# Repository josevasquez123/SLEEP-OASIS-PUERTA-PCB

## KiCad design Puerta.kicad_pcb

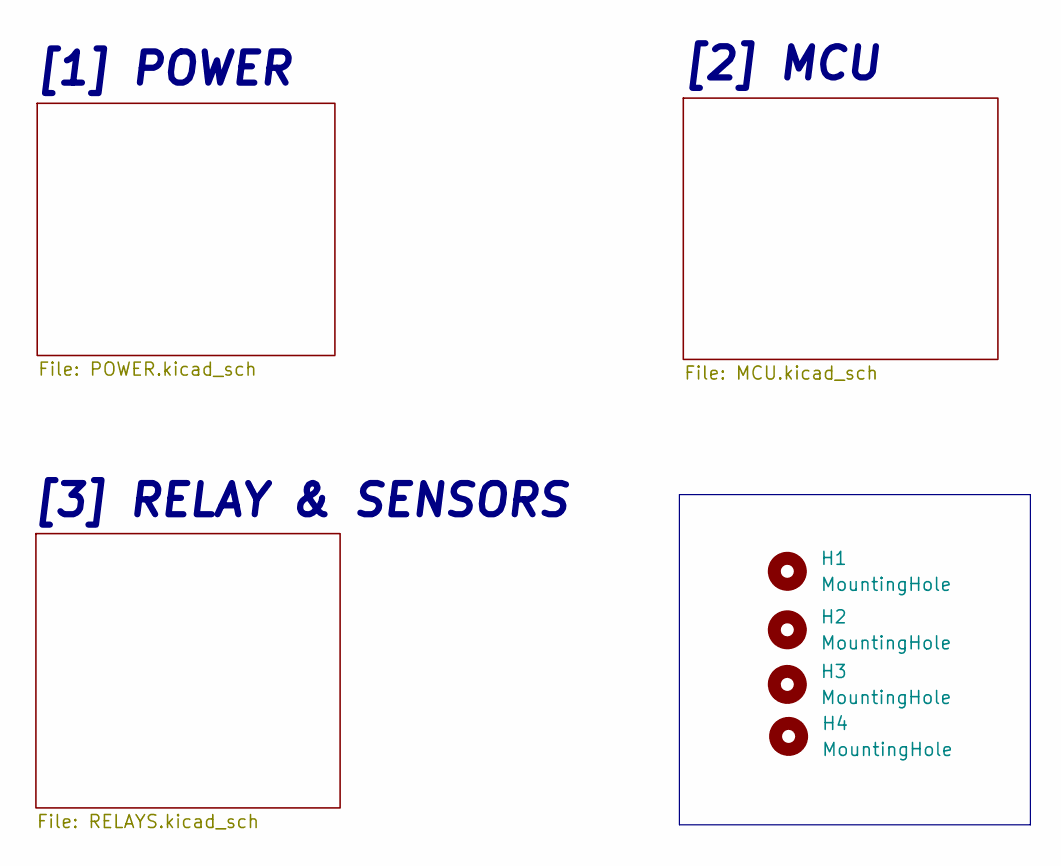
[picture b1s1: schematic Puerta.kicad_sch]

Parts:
H1, H2, H3, H4: MountingHole; MountingHole_3.2mm_M3

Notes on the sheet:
[1] POWER
[3] RELAY & SENSORS
[2] MCU

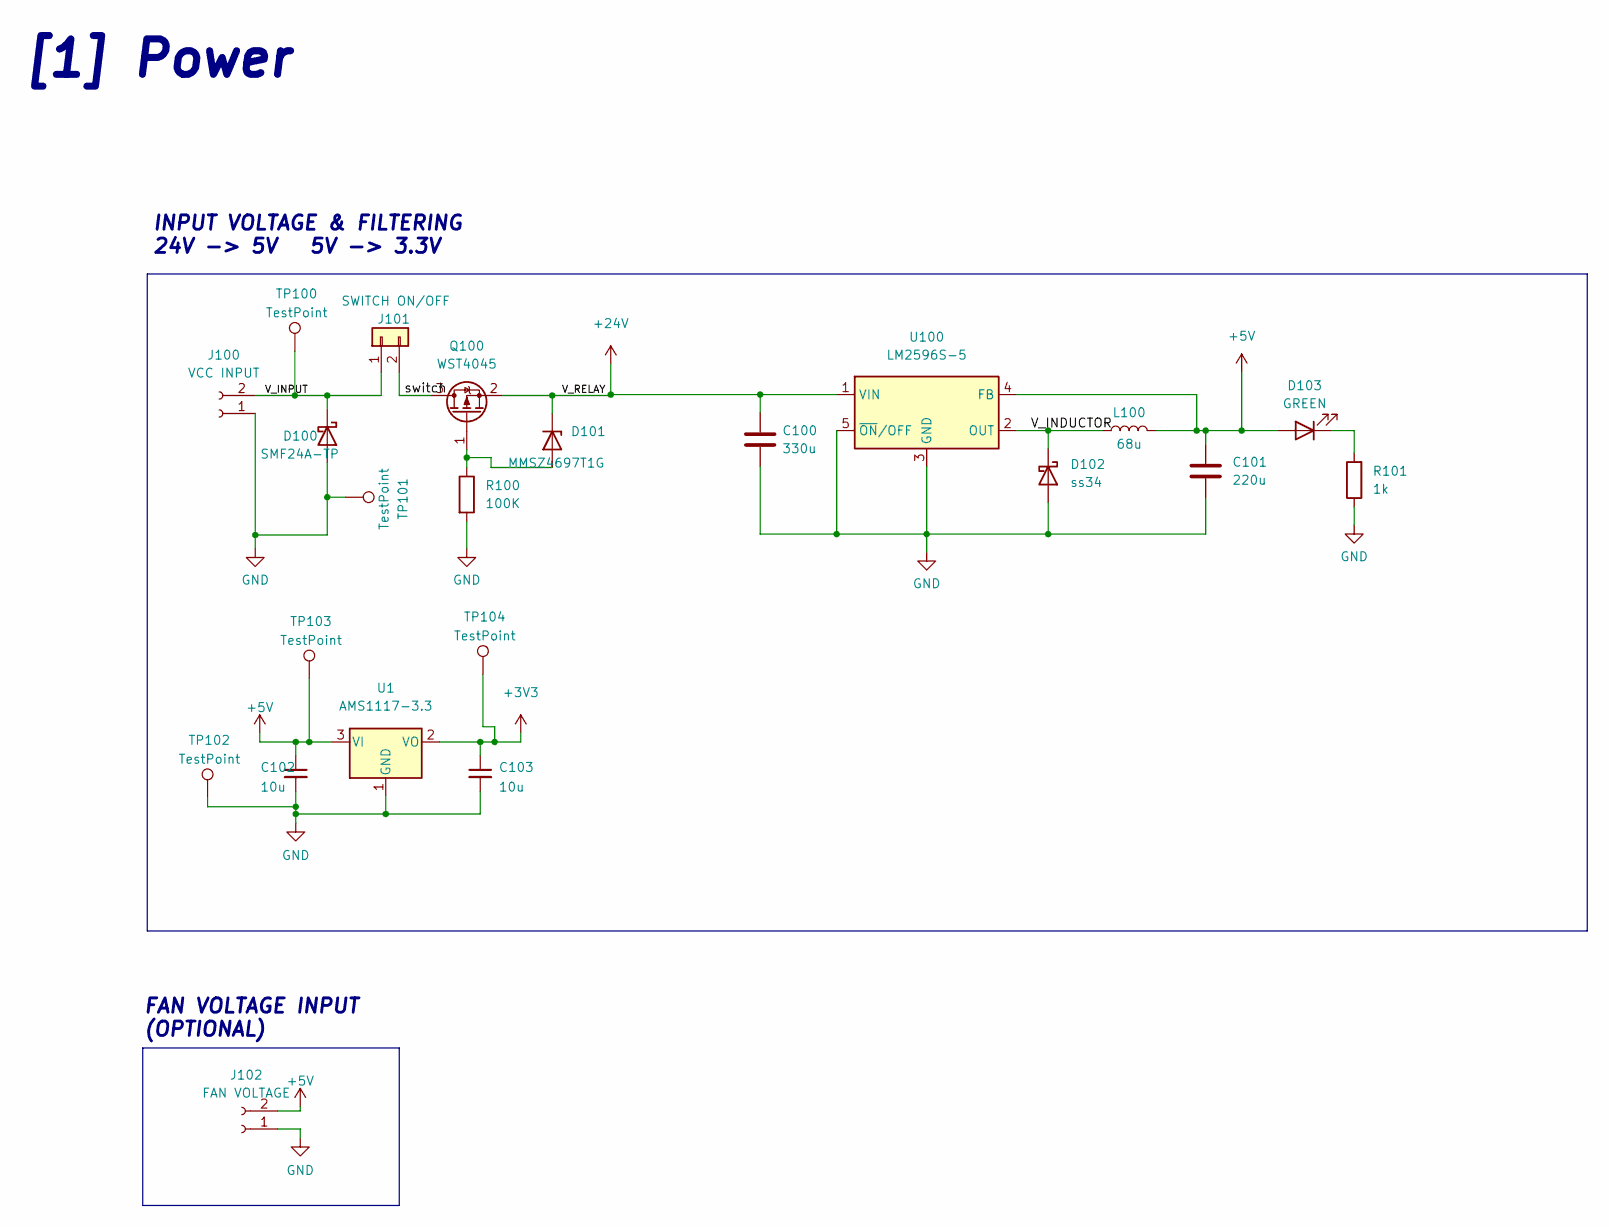
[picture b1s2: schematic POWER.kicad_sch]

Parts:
C100: 330u; C_Elec_10x10.2; LCSC C239324
C101: 220u; CP_Elec_10x10.5; LCSC C2886113
C102, C103: 10u; C_0805_2012Metric; LCSC C15850
D100: SMF24A-TP; SOD_123FL; LCSC C545276
D101: MMSZ4697T1G; D_SOD-123; LCSC C48870
D102: ss34; D_SMA; LCSC C8678
D103: GREEN; LED_0603_1608Metric; LCSC C72043
J100: VCC INPUT; PhoenixContact_MSTBA_2,5_2-G-5,08_1x02_P5.08mm_Horizontal
J101: SWITCH ON/OFF; JST_B2B-XH-A_LF__SN_
J102: FAN VOLTAGE; PinHeader_1x02_P2.54mm_Vertical
L100: 68u; L_12.3x12.3; LCSC C2929504
Q100: WST4045; SOT-23; LCSC C719073
R100: 100K; R_1206_3216Metric; LCSC C17900
R101: 1k; R_0603_1608Metric; LCSC C21190
TP100, TP101, TP102, TP103, TP104: TestPoint; TestPoint_Pad_D2.0mm
U1: AMS1117-3.3; SOT-223-3_TabPin2; LCSC C6186
U100: LM2596S-5; TO-263-5_TabPin3

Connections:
+5V: C101.1, C102.1, D103.2 (A), J102.2, L100.2, TP103.1, U1.3 (VI), U100.4 (FB); also elsewhere on the board
+24V: C100.1, D101.1 (K), Q100.2 (S), U100.1 (VIN); also elsewhere on the board
/POWER/V_INDUCTOR: D102.1 (K), L100.1, U100.2 (OUT)
/POWER/V_INPUT: D100.1 (K), J100.2, J101.1, TP100.1
/POWER/switch: J101.2, Q100.3 (D)
GND: C100.2, C101.2, C102.2, C103.2, D100.2 (A), D102.2 (A), J100.1, J102.1, R100.2, R101.1, TP101.1, TP102.1, U1.1 (GND), U100.3 (GND), U100.5 (~ON/OFF); also elsewhere on the board
unnamed: D101.2 (A), Q100.1 (G), R100.1
unnamed: D103.1 (K), R101.2

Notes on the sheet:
INPUT VOLTAGE & FILTERING 24V -> 5V 5V -> 3.3V
FAN VOLTAGE INPUT (OPTIONAL)
[1] Power

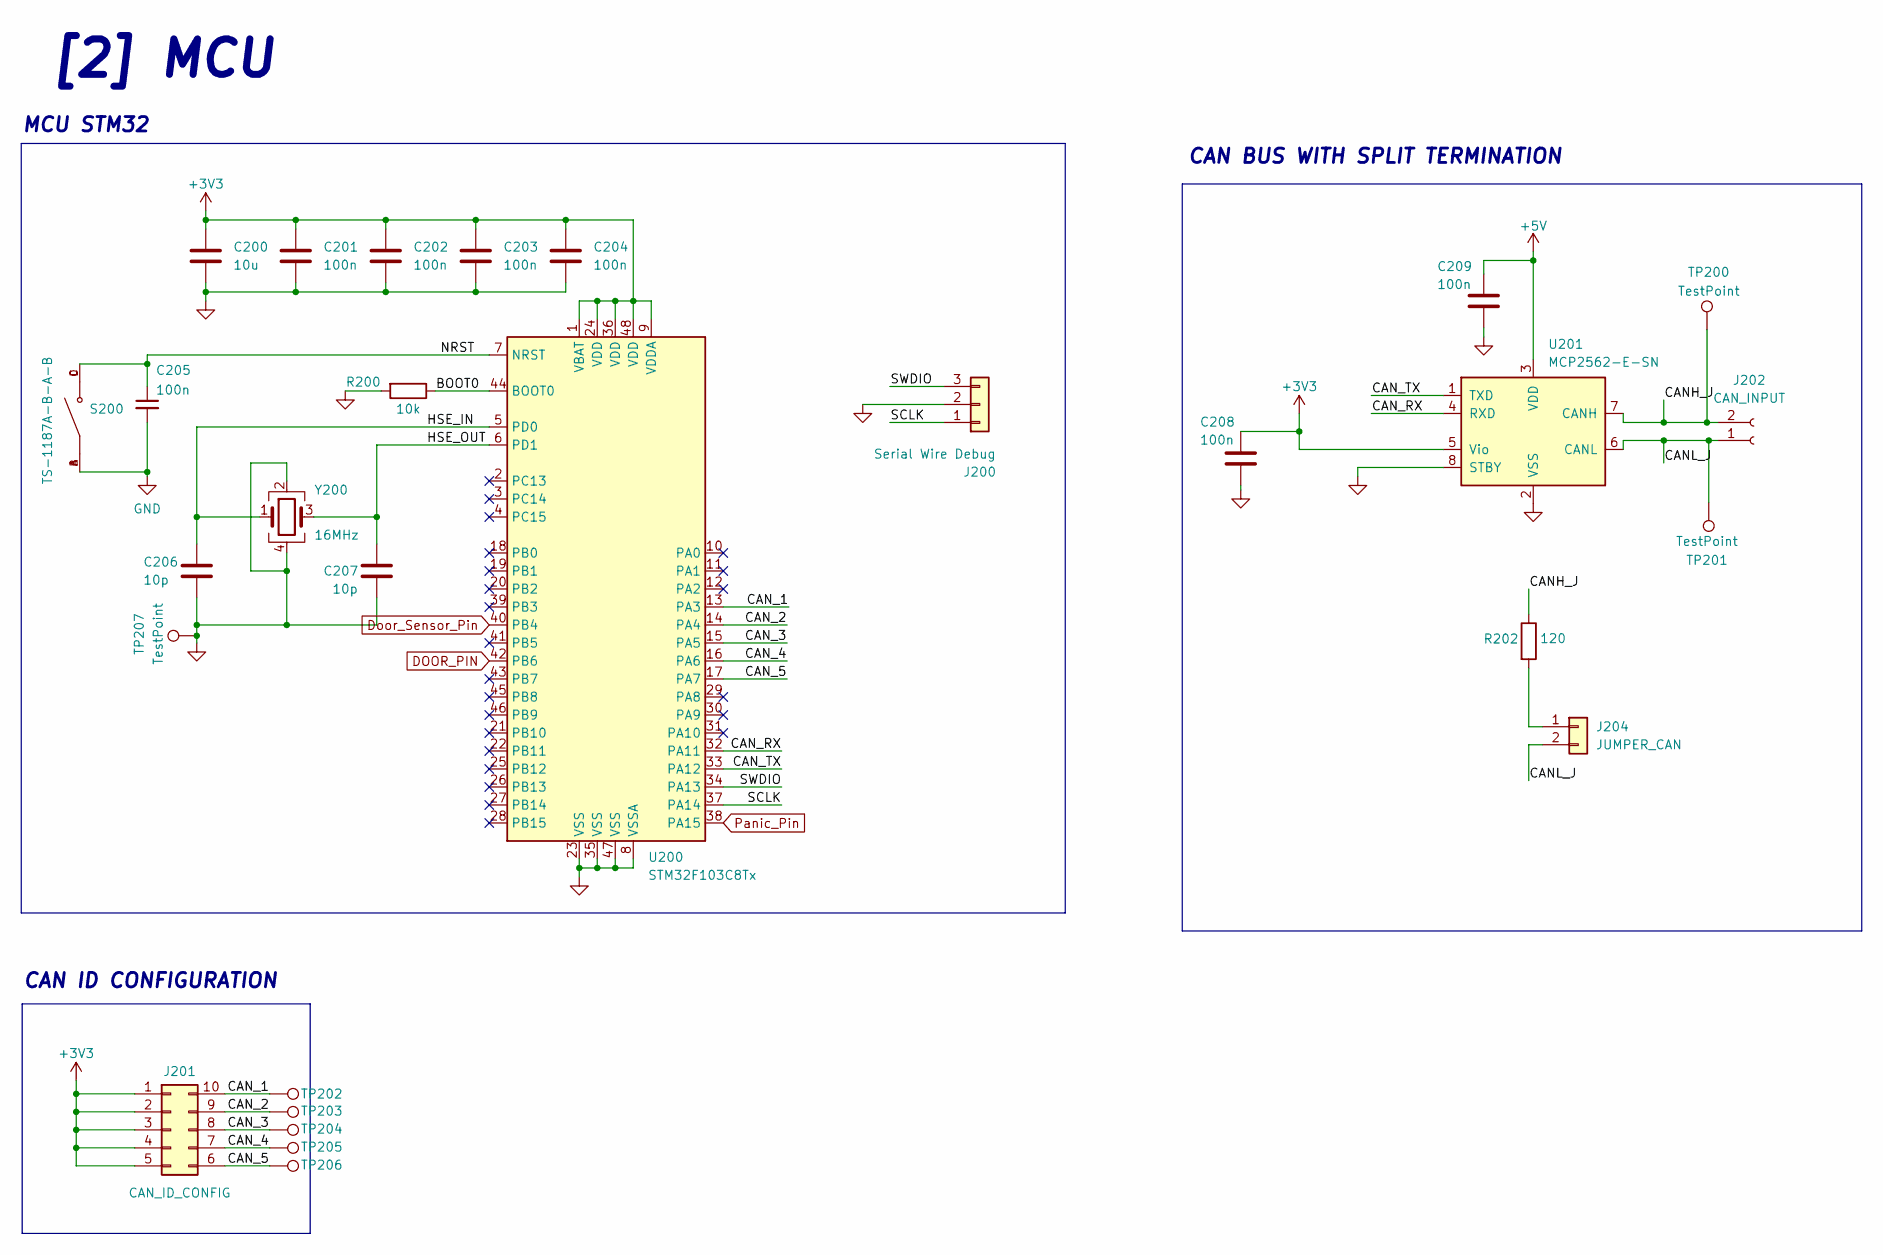
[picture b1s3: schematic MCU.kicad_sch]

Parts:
C200: 10u; C_0603_1608Metric; LCSC C19702
C201, C202, C203, C204, C205, C208, C209: 100n; C_0402_1005Metric; LCSC C1525
C206, C207: 10p; C_0402_1005Metric; LCSC C32949
J200: Serial Wire Debug; PinSocket_1x03_P2.54mm_Vertical
J201: CAN_ID_CONFIG; SW_DIP_SPSTx05_Slide_9.78x14.88mm_W7.62mm_P2.54mm
J202: CAN_INPUT; PhoenixContact_MSTBA_2,5_2-G-5,08_1x02_P5.08mm_Horizontal
J204: JUMPER_CAN; PinHeader_1x02_P2.54mm_Vertical
R200: 10k; R_0402_1005Metric; LCSC C25744
R202: 120; R_0805_2012Metric; LCSC C17437
S200: TS-1187A-B-A-B; SWITCH_SMD; LCSC C318884
TP200, TP201, TP202, TP203, TP204, TP205, TP206, TP207: TestPoint; TestPoint_Pad_D2.0mm
U200: STM32F103C8Tx; LQFP-48_7x7mm_P0.5mm
U201: MCP2562-E-SN; SOIC-8_3.9x4.9mm_P1.27mm; LCSC C191417
Y200: 16MHz; Crystal_SMD_3225-4Pin_3.2x2.5mm; LCSC C13738

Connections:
+5V: C209.1, U201.3 (VDD); also elsewhere on the board
/MCU/BOOT0: R200.1, U200.44 (BOOT0)
/MCU/CANH_J: J202.2, R202.1, TP200.1, U201.7 (CANH)
/MCU/CANL_J: J202.1, J204.2, TP201.1, U201.6 (CANL)
/MCU/CAN_1: J201.10, TP202.1, U200.13 (PA3)
/MCU/CAN_2: J201.9, TP203.1, U200.14 (PA4)
/MCU/CAN_3: J201.8, TP204.1, U200.15 (PA5)
/MCU/CAN_4: J201.7, TP205.1, U200.16 (PA6)
/MCU/CAN_5: J201.6, TP206.1, U200.17 (PA7)
/MCU/CAN_RX: U200.32 (PA11), U201.4 (RXD)
/MCU/CAN_TX: U200.33 (PA12), U201.1 (TXD)
/MCU/HSE_IN: C206.1, U200.5 (PD0), Y200.1
/MCU/HSE_OUT: C207.1, U200.6 (PD1), Y200.3
/MCU/NRST: C205.1, S200.C, S200.D, U200.7 (NRST)
/MCU/SCLK: J200.1, U200.37 (PA14)
/MCU/SWDIO: J200.3, U200.34 (PA13)
DOOR_PIN: U200.42 (PB6); also elsewhere on the board
Door_Sensor_Pin: U200.40 (PB4); also elsewhere on the board
GND: C200.2, C201.2, C202.2, C203.2, C204.2, C205.2, C206.2, C207.2, C208.2, C209.2, J200.2, R200.2, S200.A, S200.B, TP207.1, U200.8 (VSSA), U200.23 (VSS), U200.35 (VSS), U200.47 (VSS), U201.2 (VSS), U201.8 (STBY), Y200.2, Y200.4; also elsewhere on the board
unnamed: J204.1, R202.2
Panic_Pin: U200.38 (PA15); also elsewhere on the board

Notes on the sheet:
[2] MCU
MCU STM32
CAN ID CONFIGURATION
CAN BUS WITH SPLIT TERMINATION

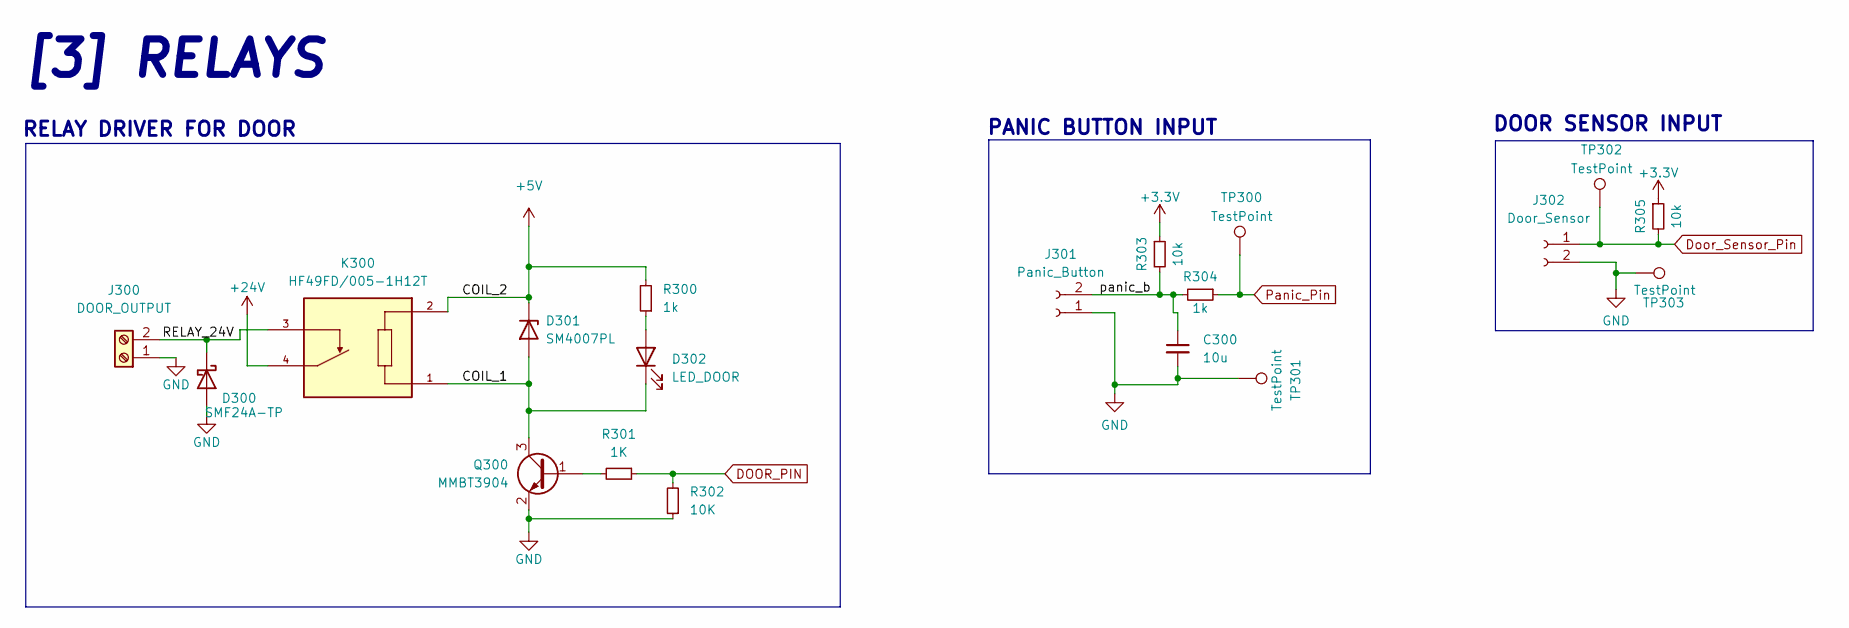
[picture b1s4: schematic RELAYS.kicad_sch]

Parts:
C300: 10u; C_0603_1608Metric; LCSC C19702
D300: SMF24A-TP; SOD_123FL; LCSC C545276
D301: SM4007PL; SOD_123FL; LCSC C64898
D302: LED_DOOR; LED_0603_1608Metric; LCSC C72038
J300: DOOR_OUTPUT; PhoenixContact_MSTBA_2,5_2-G-5,08_1x02_P5.08mm_Horizontal
J301: Panic_Button; PhoenixContact_MSTBA_2,5_2-G-5,08_1x02_P5.08mm_Horizontal
J302: Door_Sensor; PhoenixContact_MSTBA_2,5_2-G-5,08_1x02_P5.08mm_Horizontal
K300: HF49FD/005-1H12T; HF49FD0051H11F; PARTREV 1.13
Q300: MMBT3904; SOT-23; LCSC C20526
R300, R304: 1k; R_0603_1608Metric; LCSC C21190
R301: 1K; R_0603_1608Metric; LCSC C21190
R302: 10K; R_0603_1608Metric; LCSC C25804
R303, R305: 10k; R_0603_1608Metric; LCSC C25804
TP300, TP301, TP302, TP303: TestPoint; TestPoint_Pad_D2.0mm

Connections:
+5V: D301.1 (K), K300.2, R300.2; also elsewhere on the board
+24V: K300.4; also elsewhere on the board
/RELAYS&INPUTS/COIL_1: D301.2 (A), D302.1 (K), K300.1, Q300.3 (C)
/RELAYS&INPUTS/RELAY_24V: D300.1 (K), J300.2, K300.3
/RELAYS&INPUTS/panic_b: C300.1, J301.2, R303.2, R304.2
DOOR_PIN: R301.1, R302.2; also elsewhere on the board
Door_Sensor_Pin: J302.1, R305.2, TP302.1; also elsewhere on the board
GND: C300.2, D300.2 (A), J300.1, J301.1, J302.2, Q300.2 (E), R302.1, TP301.1, TP303.1; also elsewhere on the board
unnamed: D302.2 (A), R300.1
unnamed: Q300.1 (B), R301.2
Panic_Pin: R304.1, TP300.1; also elsewhere on the board

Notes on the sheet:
DOOR SENSOR INPUT
PANIC BUTTON INPUT
[3] RELAYS
RELAY DRIVER FOR DOOR

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
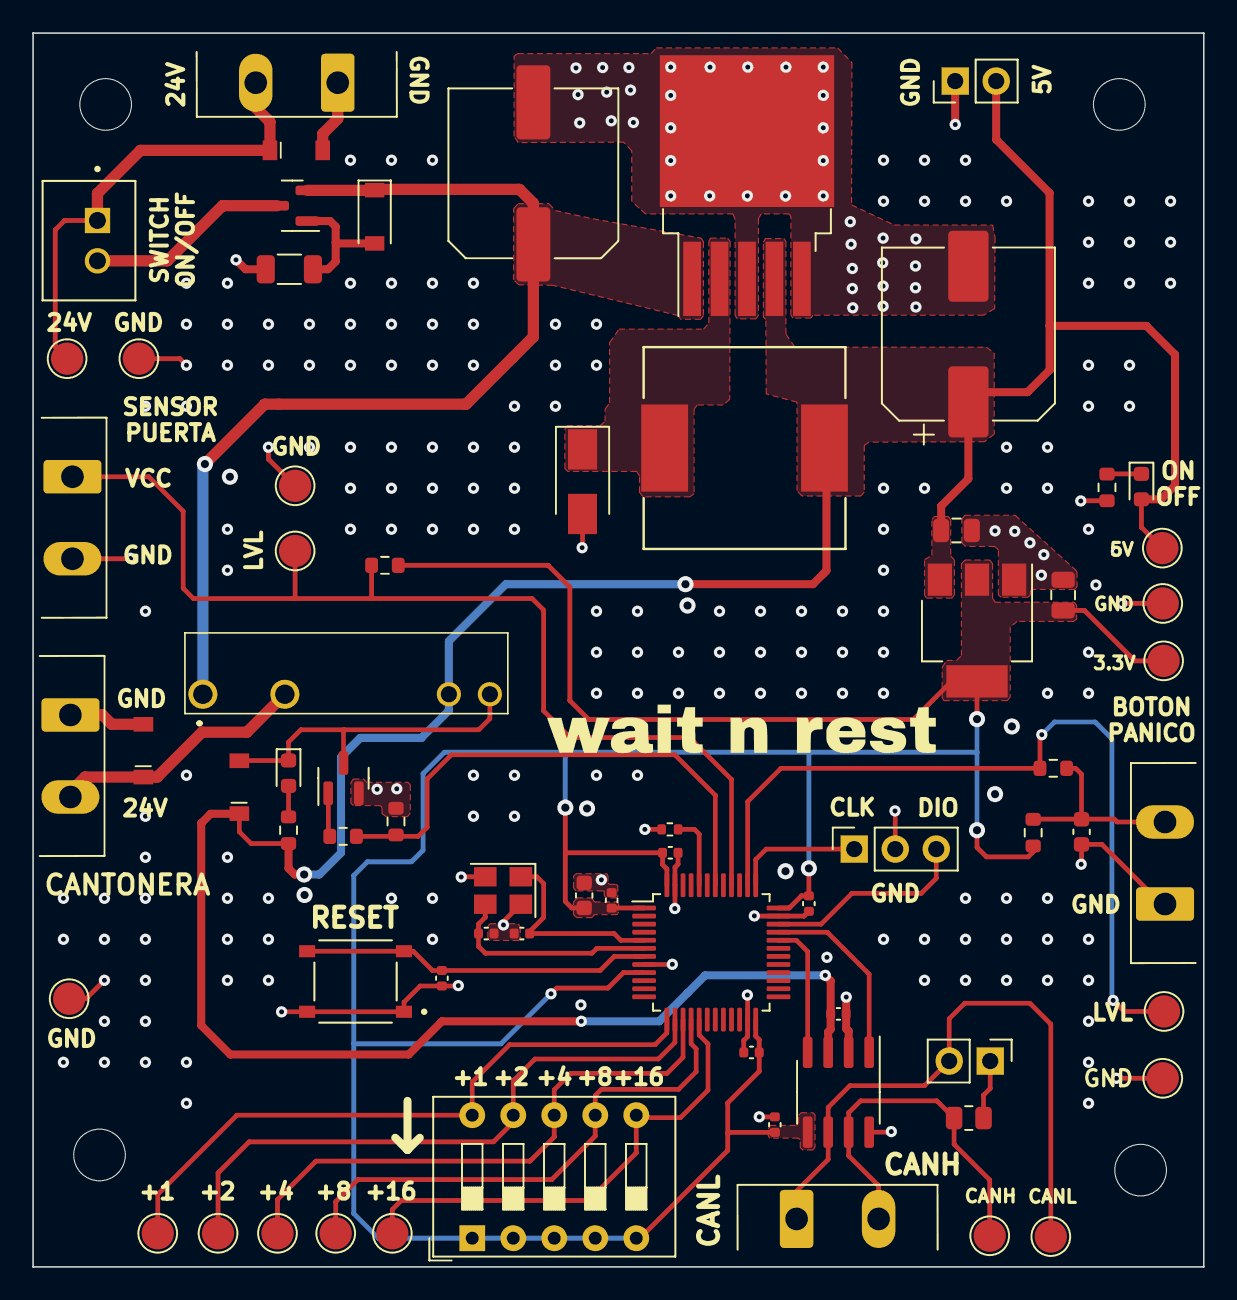
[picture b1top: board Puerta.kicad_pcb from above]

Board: 4 copper layers, 72.5 x 76.4 mm, 73 parts (0 on the bottom side), 33 nets.

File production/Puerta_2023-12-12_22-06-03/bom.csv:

Designator,Footprint,Quantity,Value,LCSC Part #
C100,C_Elec_10x10.2,1,330u,C239324
C101,CP_Elec_10x10.5,1,220u,C2886113
"C102, C103",0805,2,10u,C15850
"C200, C300",0603,2,10u,C19702
"C201, C202, C203, C204, C205, C208, C209",0402,7,100n,C1525
"C206, C207",0402,2,10p,C32949
"D100, D300",SOD_123FL,2,SMF24A-TP,C545276
D101,D_SOD-123,1,MMSZ4697T1G,C48870
D102,D_SMA,1,ss34,C8678
D103,0603,1,GREEN,C72043
D301,SOD_123FL,1,SM4007PL,C64898
D302,0603,1,LED_DOOR,C72038
"H1, H2, H3, H4",MountingHole_3.2mm_M3,4,MountingHole,
J100,"PhoenixContact_MSTBA_2,5_2-G-5,08_1x02_P5.08mm_Horizontal",1,VCC INPUT,
J101,PinHeader_1x02_P2.54mm_Vertical,1,SWITCH ON/OFF,
J102,PinHeader_1x02_P2.54mm_Vertical,1,FAN VOLTAGE,
J200,PinSocket_1x03_P2.54mm_Vertical,1,Serial Wire Debug,
J201,SW_DIP_SPSTx05_Slide_9.78x14.88mm_W7.62mm_P2.54mm,1,CAN_ID_CONFIG,
J202,"PhoenixContact_MSTBA_2,5_2-G-5,08_1x02_P5.08mm_Horizontal",1,CAN_INPUT,
J204,PinHeader_1x02_P2.54mm_Vertical,1,JUMPER_CAN,
J300,"PhoenixContact_MSTBA_2,5_2-G-5,08_1x02_P5.08mm_Horizontal",1,DOOR_OUTPUT,
J301,"PhoenixContact_MSTBA_2,5_2-G-5,08_1x02_P5.08mm_Horizontal",1,Panic_Button,
J302,"PhoenixContact_MSTBA_2,5_2-G-5,08_1x02_P5.08mm_Horizontal",1,Door_Sensor,
K300,HF49FD0051H11F,1,HF49FD/005-1H12T,
L100,SMD_12.3X12.3mm,1,68u,C2929504
Q100,SOT-23,1,WST4045,C719073
Q300,SOT-23,1,MMBT3904,C20526
R100,1206,1,100K,C17900
"R101, R300, R301, R304",0603,4,1k,C21190
R200,0402,1,10k,C25744
R202,0805,1,120,C17437
"R302, R303, R305",0603,3,10K,C25804
S200,SWITCH_SMD,1,TS-1187A-B-A-B,C318884
"TP100, TP101, TP102, TP103, TP104, TP200, TP201, TP202, TP203, TP204, TP205, TP206, TP207, TP300, TP301, TP302, TP303",TestPoint_Pad_D2.0mm,17,TestPoint,
U1,SOT-223-3_TabPin2,1,AMS1117-3.3,C6186
U100,TO-263-5_TabPin3,1,LM2596S-5,
U200,LQFP-48_7x7mm_P0.5mm,1,STM32F103C8Tx,
U201,SOIC-8_3.9x4.9mm_P1.27mm,1,MCP2562-E-SN,C191417
Y200,Crystal_SMD_3225-4Pin_3.2x2.5mm,1,16MHz,C13738

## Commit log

2023-12-11 added logo
2023-12-21 change board stackup and added logo
2024-02-19 version validada
